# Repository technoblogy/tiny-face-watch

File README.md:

# tiny-face-watch
A watch based on an ATtiny85 and a DS2417 RTC, showing the time analogue-style on a 64x48 OLED display.
For more information see: http://www.technoblogy.com/show?1OPB.

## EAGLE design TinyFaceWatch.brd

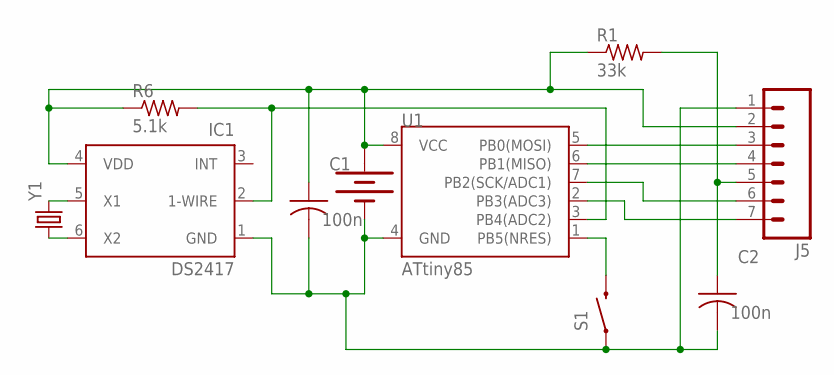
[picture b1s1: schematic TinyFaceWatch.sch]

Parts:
BAT1: 20mm coincell; BATTCON_20MM_4LEGS
C1, C2: 100n; C0805K
IC1: DS2417; TSOC6
J5: M07; 1X07
R1: 33k; M0805
R6: 5.1k; M0805
S1: SWITCH-MOMENTARY-2SMD-4.6X2.8MM; TACTILE_SWITCH_SMD_4.6X2.8MM
U1: ATtiny85; SO08-EIAJ
Y1: CRYSTAL32-SMD-MELF; CRYSTAL-32KHZ-SMD-MELF

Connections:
INT: IC1.3 (INT)
unnamed: IC1.5 (X1), Y1.X2 (2)
unnamed: IC1.6 (X2), Y1.X1 (1)
unnamed: J5.4, U1.6 (PB1(MISO))
unnamed: J5.3, U1.5 (PB0(MOSI))
unnamed: J5.6, U1.7 (PB2(SCK/ADC1))
unnamed: J5.7, U1.2 (PB3(ADC3))
unnamed: BAT1.POSITIVE@1 (+), BAT1.POSITIVE@2 (+), BAT1.POSITIVE@3 (+), BAT1.POSITIVE@4 (+), C1.1, IC1.4 (VDD), J5.2, R1.1, R6.1, U1.8 (VCC)
unnamed: C2.1, J5.5, R1.2
unnamed: BAT1.NEGATIVE (-), C1.2, C2.2, IC1.1 (GND), J5.1, S1.1, S1.2 (1), U1.4 (GND)
unnamed: S1.3 (2), S1.4 (2), U1.1 (PB5(NRES))
unnamed: IC1.2 (1-WIRE), R6.2, U1.3 (PB4(ADC2))

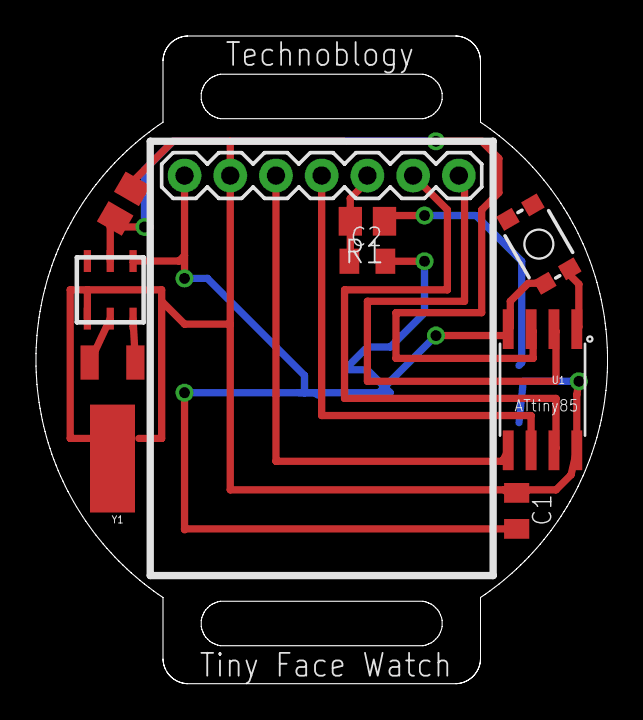
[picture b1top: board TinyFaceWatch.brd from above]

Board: 2 copper layers, 31.7 x 36.0 mm, 10 parts (1 on the bottom side), 11 nets.

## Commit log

2017-06-07 Version 1 - 7th June 2017
2017-06-07 Version 1 - Eagle files

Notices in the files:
parts and their libraries:
SparkFun-DigitalIC: Licensing: Creative Commons ShareAlike 4.0 International - https://creativecommons.org/licenses/by-sa/4.0
SparkFun-Connectors: Licensing: CC v3.0 Share-Alike You are welcome to use this library for commercial purposes.
